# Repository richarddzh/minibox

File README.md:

# Minibox

| 目录 | 内容 |
|---|---|
| [`models`](models/module-dimensions.md) | 载板两件式外壳、错位连通键盘开孔、打印文件、尺寸与避让说明 |
| [`model-v2`](model-v2/README.md) | 低矮改版外壳：左侧喇叭、后壁偏左三角布局（开关＋双Type-C）；[截面与视角数据报告](model-v2/fit-review.html) |
| [`assets`](assets) | 开发板[尺寸与天线图](assets/esp32s3_devkit_01.jpg)、[5.08 mm 接线端子](assets/crimp_terminal.jpg)、麦克风、功放、RTC、[TFT SPI](assets/tft_spi.jpg)、[摇杆](assets/joystick.jpg)与[三键键盘](assets/keypad.jpg)参考图片（TFT 型号与当前固件配置未核对） |
| [`docs`](docs/hardware-connections.md) | 主控、屏幕和摇杆的模块参数、GPIO 接线及供电注意事项 |
| [`kicad`](kicad/README.md) | KiCad 10 双层模块载板：[正面图例](kicad/renders/minibox-carrier-front-legend.png)、[背面图例](kicad/renders/minibox-carrier-back-legend.png)、GPIO 丝印与 Gerber；实物核对后方可制板 |
| [`esp32_idf_s3n16r8`](esp32_idf_s3n16r8/README.md) | ESP32-S3 N16R8 的 LVGL 闲聊闹钟、电台、设置、游戏和可选硬件自检固件 |

固件项目参考 `C:\gitroot\talking-alarm` 的 ESP-IDF 结构，独立构建，
不依赖该目录；默认启动 LVGL 应用，保留 GPIO4/5/6/7 四键及 GPIO1/2 摇杆。
GPIO4 确认，闲聊中长按录音；GPIO5 在闲聊中按住录音、松开发送，
GPIO6 返回，GPIO7 辅助确认。原录放音自检通过菜单切换。
新增 [NES 模拟器](esp32_idf_s3n16r8/README.md#nes-游戏)，从本地 SPIFFS
加载用户自备的 `.nes` 游戏；游戏内 A/B 为动作键、X/Y 为 Select/Start，
同时长按 X+Y 退出，复用当前摇杆、ST7796 屏幕与 MAX98357 音频。
NES 画面为 **256×240 原生像素居中显示，不缩放**；目标 60 次/秒模拟、
最高 30 fps 显示，实际流畅度仍需实板确认。
支持 mapper 0、1、2、3、4、7、66、112、178、245；游戏文件用英文名称，
已配置的标题在设备上中英文双行显示。按用户要求，当前 10 个指定 ROM
随仓库提供以便异地复现；私密配置、存档和分区镜像仍不纳入 Git。
菜单四方向、NES 八方向；NES 直向容错更宽，斜向要求两轴各至少 40%、
副轴/主轴至少 85%，边界隔离区不动作。
[摇杆规则与前后区域图](esp32_idf_s3n16r8/README.md#nes-摇杆活跃区域旧版与新版)
及 [ROM 列表](esp32_idf_s3n16r8/README.md#rom-来源记录) 见固件说明。
实现取舍与验收边界见 [NES 详细计划](docs/nes-implementation-plan.md)。
当前接线为 RTC SDA=GPIO15、SCL=GPIO16，INMP441 SD=GPIO21，
MAX98357 GAIN=GPIO42、SD/MODE=GPIO47；GPIO17 悬空 NC，
摇杆按压焊脚保持 NC，GPIO42 不用于摇杆按压。

16 MiB Flash 已分配：启动/系统区域 64 KiB、应用 2 MiB、
字体文件系统 10 MiB、游戏与配置文件系统 3.9375 MiB。
分区内空闲空间不会自动借给其他分区；8 MiB PSRAM 是易失运行内存。
完整布局与更新注意事项见 [显示与存储说明](docs/display-fonts.md#文件系统分区)。
仅更新固件使用 `idf.py -p COM8 app-flash`；完整 `flash` 或 `storage-flash`
会覆盖设备 storage 中的配置和存档，须先备份。

模型文档中的导出和检查命令均在 `models` 目录执行：

```powershell
Set-Location C:\gitroot\minibox\models
python -m unittest discover -s .\tests -p test_mesh_checks.py
```

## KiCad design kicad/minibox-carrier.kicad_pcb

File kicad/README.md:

# Minibox carrier v1.2 — 2026-10-10

This is the user's actual `kicad` carrier, not the separate integrated design.
Open `minibox-carrier.kicad_pro` in KiCad 10. There is **no schematic**:
PCB DRC/net checks do not constitute ERC or schematic-parity verification.
The direct-solder revision is implemented; final review is documented in
[the Chinese HTML guide](carrier-revision.html) and [revision checklist](layout-revision-plan.md).
**Engineering-review files are not permission to manufacture or order.**

## Layout and parts

The board is **94.5 × 117 mm, R5**, four copper layers, nominal 1.6 mm.
Four Ø3.0 mm NPTH holes have **84.5 × 107 mm** center spacing;
KiCad centers are (10,8), (94.5,8), (10,115), (94.5,115) mm.
Each hole has a 3.5 mm-radius/square conservative all-layer copper keepout.
Ø3.0 mm is a tight M3 fit: check screw size/tolerance and the new enclosure.
Bounding-rectangle area is only 1.28% smaller than the old 100 × 112 mm board.

| Placement | Required reservation |
|---|---|
| ESP32 | USB left, antenna right; estimated body stays inside PCB |
| RTC | Upright, battery included in 27.5 × 12 mm reservation; 3.03 mm to ESP32 estimate |
| MAX98357 | Flat 27 × 24 mm reservation; bottom Y=72, above keycap top Y=80.5 |
| Red boundary | Y=76; upper bodies ≤74, lower operation envelopes ≥78 |
| Joystick JS1 | Vertical, center (16.8,95.5); **30 mm diameter** motion may overhang 3.20 mm; body/pad copper retain ≥1 mm to the left copper boundary |
| Microphone | Center (44.455,90.25), Ø19.5 mm envelope; top Y80.5; horizontal maximin clearance to all keycaps and joystick motion is approximately 3.40 mm |
| Four keys | Standard 19.05 mm pitch both ways; lower row moves right 1.425 mm, retaining 8.10 mm left stagger and 0.20 mm to the screw square |
| Keycaps | Maximum accepted envelope 18 × 18 mm; neighboring gap 1.05 mm |
| Wire entries | J8/J9 left, J7 right; external wire/tool clearance still requires a fit check |

SW1–SW4 use **HanElectricity CPG151101D13 / C49234235**; JS1 uses
**YTL YV13S-L7.85-B10Ka(60)-0-DL01 / C37323747**.
Their local footprints are traced to the exact linked drawings, not generic
MX/joystick substitutes. The joystick has a press mechanism but **it is intentionally
unused**; switch and mounting leads have no net; **GPIO42 now controls amplifier GAIN**.
Reference PDFs and layout images are in [`hardware_references`](../hardware_references/carrier-revision-references.md).
The exact parts lack precise supplied 3D models; renders must not be mistaken
for complete assembled-product models. Module envelopes and keycap size are
acceptance reservations, not measured/verified models.

J11/J12 cable sockets are removed. Remaining female strips: 1×22 two,
1×14 one, 1×7 one, 1×6 one, **1×3 two**, totaling seven strips/77 contacts.
J3 is two separate 1×3 sockets, row spacing 7.62 mm, **not** a normal 2×3 socket.
Three 5.08 mm screw terminals, four direct-solder switches, one direct-solder
joystick, and two 0402 resistors complete the assembly. All components install
from the front; THT leads solder from the back.
J7 is **KANGNEX WJ500V-5.08-03P-14-00A / C72334**; J8/J9 are
**WJ500V-5.08-2P / C8465**. Exact local footprints include the 0.60 mm joining
lug, 10 mm body depth, 14.07 mm height, and a tolerance-aware courtyard.
J8/J9 move left2.5/up3.94 mm from the prior version, with anchors
(11.5,48.56)/(11.5,61.06). J8's actual body top aligns with the estimated
ESP32 body bottom at Y45.97; their wire entries and electrical order are unchanged.
The selected terminal holes are **Ø1.50 mm**, with unchanged Ø2.60 mm pads
and 0.55 mm radial annular rings. No original Phoenix 3D model is reused
to impersonate the selected WJ500V; current renders show its holes/outline,
not an exact terminal body.

## GPIO and Type-C

Keys → GPIO4/5/6/7 (active-low, internal pulls); RTC SDA/SCL →15/16;
MIC_SD →21; amplifier GAIN/SD_MODE →42/47; GPIO17 is NC. I2S WS/BCLK/DIN →39/40/41;
joystick VR1/VR2 wipers →1/2; LCD remains GPIO9–14.
Actual front silkscreen identifies each module/terminal signal and its GPIO
using digits only, for example `SDA15`, `BCLK40`, `DIN41`, and `KEY1 4`.
Power pins retain `3V3`/`5V`/`GND`; disconnected pins retain `NC`.
Labels are on `F.SilkS`, not just the non-printing fabrication layer.
See [the authoritative wiring table](../docs/hardware-connections.md).
RTC front-view order is CLK/INT/SCL/SDA/3V3/GND; only functional net names
and labels changed, retaining both original copper paths. INMP441 front-view
left top-to-bottom is L/R(GND), WS39, SCK40; right is GND, 3V3, SD21.
The lower-row centre reaches approximately58% of the upper-left key width:
the requested approximate2/3 position would overlap the lower-right screw square
with18 mm keycaps. The screw exclusion takes priority without moving the hole.
The joystick's leftmost pad copper is X7.22 mm:1.22 mm from the X6 mm
copper-pour boundary and2.22 mm from the board edge. The body gap is1.05 mm.
Octal-memory GPIO35/36/37 are unused, as are USB19/20 and UART43/44.
GPIO39–42 cannot simultaneously be used for external four-wire JTAG.
Actual clone RGB firmware remains GPIO48; official v1.1 uses38, requiring
physical board identification, not an automatic firmware change.
The requested independent GPIO audit checked all44 J1/J2 pads against the
[official v1.1 J1/J3 table](https://docs.espressif.com/projects/esp-dev-kits/zh_CN/latest/esp32s3/esp32-s3-devkitc-1/user_guide_v1.1.html#j3):
no mapping errors or peripheral conflicts were found. Verify the clone's
actual pinout/RGB before production. The user has tested the actual INMP441
module and confirmed no additional SD pull-down is needed; keep the carrier,
firmware and BOM unchanged. This does not establish the module's internal
resistor arrangement or apply to other module variants.

External Type-C VBUS/GND →J8; independent CC1/CC2 →J9 pads1/2.
R1/R2 each pull their own CC to GND through **5.1 kΩ, 0402, 1%**.
Do not short CC1/CC2 or parallel Rd already present on a Type-C breakout.
This identifies a ordinary **5 V sink**, not USB-PD or a 3 A guarantee.
No USB data traces are routed. Check regulator current and USB/external-5V
backfeeding before connecting two sources.

## Routing and manufacturing review

F.Cu signals/GND; In1 continuous GND; In2 separated power corridors/GND;
B.Cu signals/GND. I2S prefers F.Cu/In1, with limited B.Cu/In2-ground-reference
branches. The router checks actual filled reference copper every ≤0.1 mm
outside necessary same-net antipads and requires one connected In1 region.
Signal vias receive nearby GND stitching. This is not a signal-integrity test.
Ground stitching was pruned from41 to23 vias after rerouting;18 redundant
vias were removed, with candidate-by-candidate connectivity/refill checks.
The current manifest records the final counts: retain return paths within
3 mm of every signal/power via and connections to separate ground-copper regions.
Do not add periodic stitching along same-layer I2S traces merely for their length;
the continuous reference plane carries their return current.

Signals/clearance **0.20/0.20 mm**, 3V3 feeders0.65 mm, 5V feeders0.80 mm;
ordinary vias **0.60/0.30 mm**. Copper-edge0.50 mm; PTH hole spacing0.45 mm;
Track-to-other-net pad clearance is **0.30 mm**, or **0.50 mm** at 5V pads.
The upper keys retain their previous positions; rightmost keycap-to-edge gap0.60 mm.
These tighter mechanical edge margins require an enclosure/cap tolerance check.
silk ≥1.0 mm with0.15 mm strokes. Header holes1.0/pads1.7 mm;
terminal holes1.5/pads2.6 mm; switch holes1.5/pads2.1 mm.
Do not treat signal width or these power feeders as a 3 A qualification.
Actual factory stackup/copper thickness, temperature rise and power bottlenecks
remain review items. [Domestic JLC capability rules](../docs/jlc-pcb-design-spec.md)
distinguish limits from recommendations.

Actual latest DRC/mechanical metrics and hashes belong in
`assembly\manifest.json` and `drc.json`;
an absent report or failed gate means export is incomplete.
Only a clean saved board may pass `export_revision.py`.
The exporter checks all plated-pad/via centers on all four copper CAM layers
against the saved PCB, and checks PTH/NPTH drill coordinates and diameters using
the same lower-left origin. This is digital alignment, not factory registration certification.
R1/R2 use verified UNI-ROYAL 0402WGF5101TCE/C25905, 5.1 kΩ ±1%;
domestic catalog stock is not reserved. Full-assembly BOM now identifies all
17 physical pieces with C numbers, including the five LAIL female-strip sizes.
Factory insertion/soldering approval, actual fit and final supply leave the BOM
**review-only**, even if DRC is clean.

### JLC placement-library mapping

Use `assembly\positions-jlc-review.csv` for the selected
domestic JLC library, together with the full BOM and the unchanged Gerber ZIP.
`positions-all-review.csv` records KiCad pad centres/footprint angles; it is
**not directly interchangeable** with the JLC file. In the factory library,
the seven female strips have a different zero angle and JS1 has a different
head datum. The exporter fits numbered library pads to actual saved PCB pads,
including the two separate J3 strips, and rejects mismatched parts or geometry.
`jlc-placement-review.json` records each angle, origin and pad-fit residual.
It also records the KiCad centre/angle and the factory origin/angle corrections.
`jlc-saved-placement.json` preserves the actual factory-saved, refreshed readback
for this board hash. Generated placements are checked against that snapshot at
the website's coordinate precision. After changing the layout, regenerate from
the new PCB: reuse library datum definitions, never copy old absolute positions.
The old snapshot is then historical evidence, not approval of the new layout.

This corrects assembly instructions, not copper or holes. Gerber has no
component-library rotation/model mapping; do not rotate PCB footprints or
change Gerber geometry to repair a factory preview. Missing J4/J6 3D models
are not missing parts. Verify the website's rotation convention and saved
positions against the actual Gerber pads before approving factory DFM.
The files remain engineering review inputs, not production approval.

Regenerate only these placement files without rerouting or re-exporting CAM:

```powershell
& 'C:\Program Files\KiCad\10.0\bin\python.exe' .\kicad\export_jlc_positions.py
```

## Current outputs and Git history

| Current revision | Purpose |
|---|---|
| `renders\assembly-layout.svg` | Reservation layout, not exact assembled geometry |
| `renders\minibox-carrier-front.png` / `back.png` | Genuine saved-board renders |
| `renders\minibox-carrier-isometric.png` | Genuine saved-board perspective |
| `renders\minibox-carrier-front-legend.png` / `back-legend.png` | Current Chinese material legends and board/hole dimensions |
| `assembly` | DRC, manifest, SMT BOM/CPL, separate THT positions, pin map |
| `fabrication` | Four-copper-layer Gerbers and separate PTH/NPTH drills |
| `fabrication\minibox-gerber-review.zip` | PCB CAM review archive |

Only fixed current paths are retained. Previous quote CSVs, dated revision
directories and older archives are recoverable from Git history, not alternate
submission inputs. The manifest records PCB/artifact hashes rather than a date
as a version identifier. Do not embed the current commit SHA in generated files:
it would describe the pre-export commit and change again when those files commit.
No order, upload, purchase or payment is authorized by these files.

## Reproducible commands

From `C:\gitroot\minibox`, after explicitly backing up the routed board:

```powershell
& 'C:\Program Files\KiCad\10.0\bin\python.exe' .\kicad\generate_board.py --replace-routed
& 'C:\Program Files\KiCad\10.0\bin\python.exe' .\kicad\route_board.py
& 'C:\Program Files\KiCad\10.0\bin\python.exe' .\kicad\prune_ground_vias.py
& 'C:\Program Files\KiCad\10.0\bin\python.exe' .\kicad\export_revision.py
```

Generation replaces routing, so its default guard refuses to overwrite tracks.
Inspect every command's result; do not continue after a failure.
For PNGs, use KiCad `pcb render --side top|bottom --quality basic` (high is optional).
Then run `python .\kicad\add_render_legends.py`; its dimensions are read
from the saved PCB, and the legends now correctly identify four copper layers.
After updating renders or documentation, run `python .\kicad\package_review.py`
to refresh `assembly\minibox-assembly-review.zip` and all artifact hashes.
Every PCB/part change requires the full export, not only the coordinate command.
The full exporter now also renders the saved board's front/back/isometric PNGs
and regenerates both Chinese dimension/legend images before packaging.
`render_source_board_sha256` binds that render batch to the exported PCB.
After partial rerouting, the pruning command removes only redundant GND vias,
refilling and checking each candidate's connectivity and actual I2S reference
copper. It preserves a GND return via within3 mm of every signal/power via.
Its reduction report is in `assembly\ground-stitching-review.json`; run the
full export afterwards to renew DRC, renders, CAM, placements and hashes.

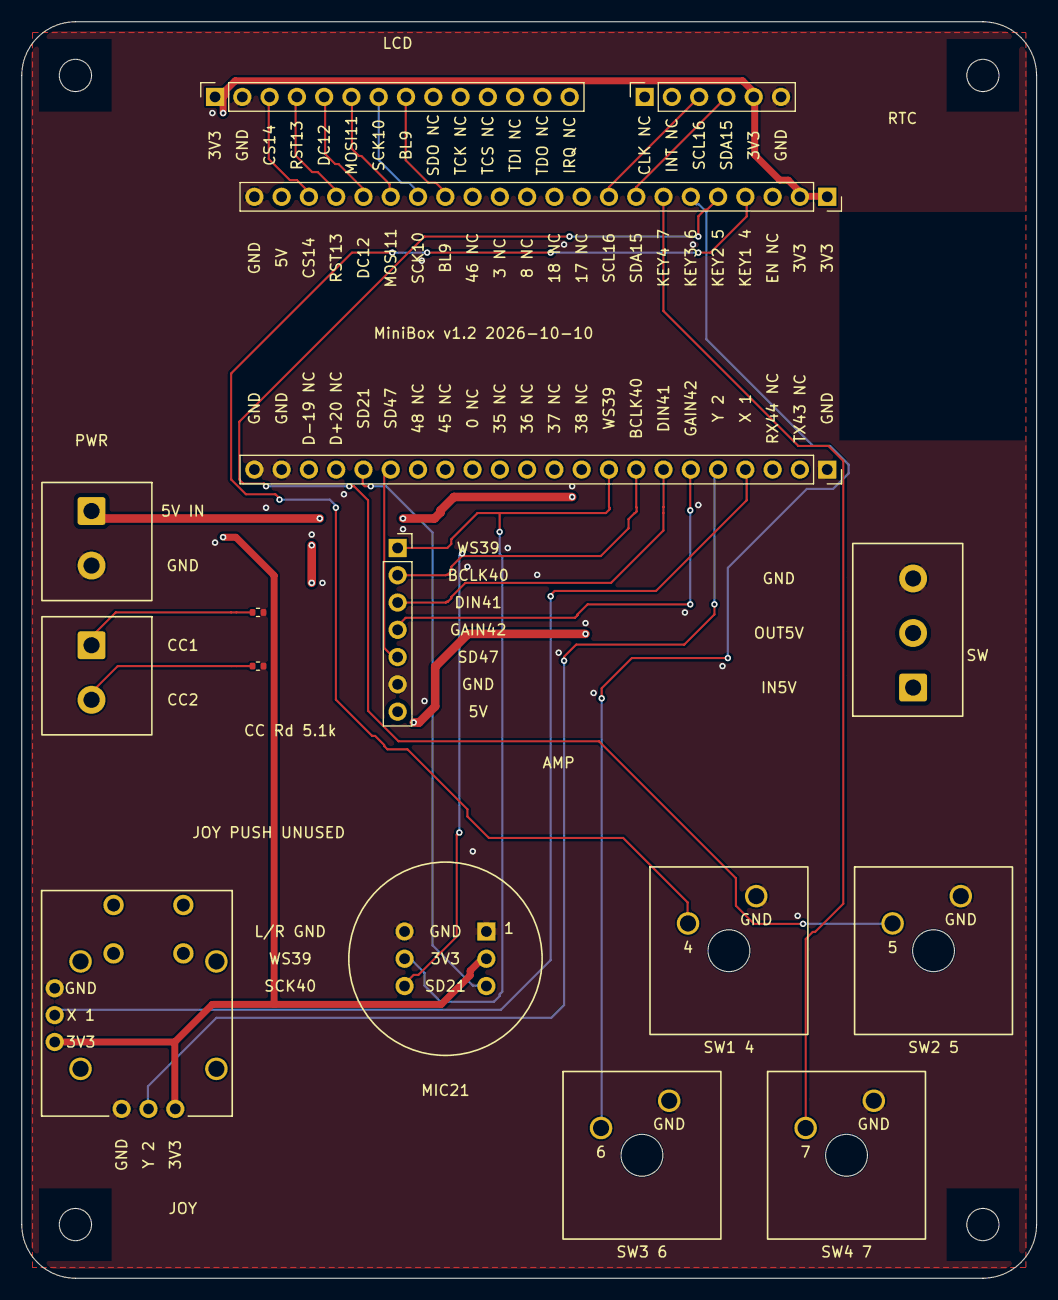
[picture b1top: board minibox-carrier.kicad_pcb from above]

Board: 4 copper layers, 94.5 x 117.0 mm, 20 parts (0 on the bottom side), 26 nets.

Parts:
H1, H2, H3, H4: M3 NPTH; MountingHole_3mm
J1: ESP32-S3 J1 - USB LEFT; PinSocket_1x22_P2.54mm_Vertical
J2: ESP32-S3 J3 - USB LEFT; PinSocket_1x22_P2.54mm_Vertical
J3: INMP441 two 1x3 sockets; INMP441_2x03_Row7.62mm
J4: MAX98357A module socket; PinSocket_1x07_P2.54mm_Vertical
J5: PCF8563T upright module; PinSocket_1x06_P2.54mm_Vertical
J6: ST7796 14-pin display; PinSocket_1x14_P2.54mm_Vertical
J7: WJ500V-5.08-03P-14-00A; WJ500V_5.08_3P
J8, J9: WJ500V-5.08-2P; WJ500V_5.08_2P
JS1: YV13S-L7.85-B10Ka(60)-0-DL01; YV13S_L7.85_B10Ka_60_0_DL01
R1, R2: 5.1k 1%; R_0402_1005Metric
SW1, SW2, SW3, SW4: CPG151101D13

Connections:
3V3: J1.1, J1.2, J3.3, J5.5, J6.1, JS1.X3, JS1.Y3
5V_IN: J7.1, J8.1
5V_SW: J1.21, J4.7, J7.2
AMP_GAIN: J2.6, J4.4
AMP_SD: J2.17, J4.5
AUDIO_DIN: J2.7, J4.3
BUTTON1: J1.4, SW1.1
BUTTON3: J1.6, SW3.1
BUTTON4: J1.7, SW4.1
GND: J1.22, J2.1, J2.21, J2.22, J3.1, J3.2, J4.6, J5.6, J6.2, J7.3, J8.2, JS1.X1, JS1.Y1, R1.2, R2.2, SW1.2, SW2.2, SW3.2, SW4.2
GPIO1: J2.4, JS1.X2
GPIO2: J2.5, JS1.Y2
I2S_BCLK: J2.8, J3.6, J4.2
I2S_WS: J2.9, J3.4, J4.1
LCD_BL: J1.15, J6.8
LCD_CS: J1.20, J6.3
LCD_DC: J1.18, J6.5
LCD_MOSI: J1.17, J6.6
LCD_RST: J1.19, J6.4
LCD_SCK: J1.16, J6.7
MIC_SD: J2.18, J3.5
RECORD: J1.5, SW2.1
RTC_SCL: J1.9, J5.3
RTC_SDA: J1.8, J5.4
USB_CC1: J9.1, R1.1
USB_CC2: J9.2, R2.1

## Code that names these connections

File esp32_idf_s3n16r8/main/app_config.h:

#pragma once

#include "sdkconfig.h"
#include <stdint.h>

#define LCD_WIDTH 480
#define LCD_HEIGHT 320
#define LCD_LED_PIN 9
#define LCD_SCK_PIN 10
#define LCD_SDI_PIN 11
#define LCD_DC_PIN 12
#define LCD_RESET_PIN 13
#define LCD_CS_PIN 14
#define LCD_SPI_HZ (CONFIG_MINIBOX_LCD_SPI_MHZ * 1000000)
#define ONBOARD_LED_PIN 48
#define AUDIO_BCLK_PIN 40
#define AUDIO_WS_PIN 39
#define MIC_SD_PIN 21
#define SPEAKER_DIN_PIN 41
#define SPEAKER_SD_MODE_PIN 47
#define SPEAKER_GAIN_PIN 42
#define AUDIO_SAMPLE_RATE 16000
#define AUDIO_MAX_SECONDS 3
#define BUTTON_1_PIN 4
#define RECORD_BUTTON_PIN 5
#define BUTTON_3_PIN 6
#define BUTTON_4_PIN 7
#define BUTTON_COUNT 4
#define RTC_SDA_PIN 15
#define RTC_SCL_PIN 16

#define MINIBOX_STRINGIFY_INNER(value) #value
#define MINIBOX_STRINGIFY(value) MINIBOX_STRINGIFY_INNER(value)
#define BUTTON_GPIO_LABELS "GPIO" MINIBOX_STRINGIFY(BUTTON_1_PIN) "/" \
                          MINIBOX_STRINGIFY(RECORD_BUTTON_PIN) "/" \
                          MINIBOX_STRINGIFY(BUTTON_3_PIN) "/" \
                          MINIBOX_STRINGIFY(BUTTON_4_PIN)
#define RECORD_GPIO_LABEL "GPIO" MINIBOX_STRINGIFY(RECORD_BUTTON_PIN)

#define JOYSTICK_X_PIN CONFIG_MINIBOX_JOYSTICK_X_PIN
#define JOYSTICK_Y_PIN CONFIG_MINIBOX_JOYSTICK_Y_PIN
#define JOYSTICK_K_PIN (-1)
#ifdef CONFIG_MINIBOX_JOYSTICK_K_ACTIVE_LOW
#define JOYSTICK_K_ACTIVE_LEVEL 0
#else
#define JOYSTICK_K_ACTIVE_LEVEL 1
#endif

_Static_assert(JOYSTICK_X_PIN != JOYSTICK_Y_PIN &&
               JOYSTICK_X_PIN != JOYSTICK_K_PIN &&
               JOYSTICK_Y_PIN != JOYSTICK_K_PIN,
               "Joystick pins must be distinct");
_Static_assert(JOYSTICK_X_PIN >= 1 && JOYSTICK_X_PIN <= 10 &&
               JOYSTICK_Y_PIN >= 1 && JOYSTICK_Y_PIN <= 10,
               "ESP32-S3 joystick axes require ADC1 GPIO1-10, not GPIO40/41");
_Static_assert(JOYSTICK_X_PIN != BUTTON_1_PIN &&
               JOYSTICK_X_PIN != RECORD_BUTTON_PIN &&
               JOYSTICK_X_PIN != BUTTON_3_PIN &&
               JOYSTICK_X_PIN != BUTTON_4_PIN &&
               JOYSTICK_Y_PIN != BUTTON_1_PIN &&
               JOYSTICK_Y_PIN != RECORD_BUTTON_PIN &&
               JOYSTICK_Y_PIN != BUTTON_3_PIN &&
               JOYSTICK_Y_PIN != BUTTON_4_PIN &&
               JOYSTICK_K_PIN != BUTTON_1_PIN &&
               JOYSTICK_K_PIN != RECORD_BUTTON_PIN &&
               JOYSTICK_K_PIN != BUTTON_3_PIN &&
               JOYSTICK_K_PIN != BUTTON_4_PIN,
               "Joystick pins must not conflict with keypad pins");
_Static_assert(MIC_SD_PIN != RTC_SDA_PIN && MIC_SD_PIN != RTC_SCL_PIN &&
               SPEAKER_SD_MODE_PIN != BUTTON_4_PIN &&
               SPEAKER_GAIN_PIN != RTC_SDA_PIN && SPEAKER_GAIN_PIN != RTC_SCL_PIN &&
               SPEAKER_SD_MODE_PIN != RTC_SDA_PIN && SPEAKER_SD_MODE_PIN != RTC_SCL_PIN,
               "Revised carrier GPIOs must not share peripheral functions");
_Static_assert(JOYSTICK_X_PIN != SPEAKER_SD_MODE_PIN &&
               JOYSTICK_Y_PIN != SPEAKER_SD_MODE_PIN &&
               JOYSTICK_K_PIN != SPEAKER_SD_MODE_PIN &&
               JOYSTICK_X_PIN != SPEAKER_GAIN_PIN &&
               JOYSTICK_Y_PIN != SPEAKER_GAIN_PIN &&
               JOYSTICK_K_PIN != SPEAKER_GAIN_PIN,
               "Joystick pins must not conflict with amplifier control pins");
_Static_assert(JOYSTICK_K_PIN != AUDIO_BCLK_PIN &&
               JOYSTICK_K_PIN != AUDIO_WS_PIN &&
               JOYSTICK_K_PIN != MIC_SD_PIN &&
               JOYSTICK_K_PIN != SPEAKER_DIN_PIN &&
               JOYSTICK_K_PIN != RTC_SDA_PIN &&
               JOYSTICK_K_PIN != RTC_SCL_PIN,
               "Joystick button must not share I2S or RTC pins");

/* Business logic uses the same physical peripherals as hardware diagnostics. */
#define APP_UI_W 320
#define APP_UI_H 240
#define APP_ONBOARD_RGB_PIN ONBOARD_LED_PIN
#define APP_BUTTON_DEBOUNCE_MS 30
#define APP_BUTTON_LONG_PRESS_MS 800
#define APP_MIC_BCLK_PIN AUDIO_BCLK_PIN
#define APP_MIC_LRCK_PIN AUDIO_WS_PIN
#define APP_MIC_DATA_PIN MIC_SD_PIN
#define APP_SPK_BCLK_PIN AUDIO_BCLK_PIN
#define APP_SPK_LRCK_PIN AUDIO_WS_PIN
#define APP_SPK_DATA_PIN SPEAKER_DIN_PIN
#define APP_VOICE_SAMPLE_RATE 16000U
#define APP_MIC_CAPTURE_RATE 16000U
#define APP_MIC_DIGITAL_GAIN 1
#define APP_VOICE_MAX_RECORD_MS 10000U
#define APP_AUDIO_ARENA_BYTES (64 * 1024)
#define APP_WIFI_CONNECT_TIMEOUT_MS 20000U
#define APP_WIFI_RETRY_MS 5000U
#define APP_TIME_REFRESH_MS 86400000U

#define APP_DOUBAO_ASR_URL \
    "wss://openspeech.bytedance.com/api/v3/sauc/bigmodel_nostream"
#define APP_DOUBAO_ASR_RESOURCE_ID "volc.seedasr.sauc.duration"
#define APP_DOUBAO_AGENT_URL \
    "https://open.feedcoopapi.com/agent_api/agent/chat/completion"
#define APP_DOUBAO_AGENT_BOT_ID "7647087216547694086"
#define APP_DOUBAO_TTS_URL \
    "https://openspeech.bytedance.com/api/v3/tts/unidirectional"
#define APP_DOUBAO_TTS_RESOURCE_ID "seed-icl-2.0"
#define APP_DOUBAO_TTS_SPEAKER "S_yOMisdm22"
#define APP_DOUBAO_TTS_SAMPLE_RATE APP_VOICE_SAMPLE_RATE

#define APP_SPIFFS_BASE_PATH "/spiffs"
#define APP_WIFI_CONFIG_PATH "/spiffs/wifi_config.txt"
#define APP_WIFI_PROFILES_PATH "/spiffs/wifi_profiles.bin"
#define APP_SECRETS_CONFIG_PATH "/spiffs/app_secrets.txt"
#define APP_PROVISION_AP_SSID "Minibox-Setup"
#define APP_PROVISION_AP_PASSWORD "minibox-setup"
#define APP_PROVISION_AP_CHANNEL 1
#define APP_PROVISION_AP_MAX_CONN 4

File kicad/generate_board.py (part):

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    "45 NC", "48 NC", "SD47", "SD21", "D+20 NC", "D-19 NC", "GND", "GND",
]
J2_NETS = [
    "GND", None, None, "GPIO1", "GPIO2", "AMP_GAIN", "AUDIO_DIN", "I2S_BCLK", "I2S_WS",
    None, None, None, None, None, None, None, "AMP_SD", "MIC_SD", None, None, "GND", "GND",
]

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power = terminal("J8", 2, 11.5, 48.56, ["5V_IN", "GND"], 270)
cc = terminal("J9", 2, 11.5, 61.06, ["USB_CC1", "USB_CC2"], 270)
joy = load("JS1", "Minibox", "YV13S_L7.85_B10Ka_60_0_DL01", 16.8, 95.5,
           {"X1": "GND", "X2": "GPIO1", "X3": "3V3",
            "Y1": "GND", "Y2": "GPIO2", "Y3": "3V3"},
           "YV13S-L7.85-B10Ka(60)-0-DL01", 270)
for i, (x, y) in enumerate(KEY_CENTERS, 1):
    load(f"SW{i}", "Minibox", "CPG151101D13", x, y,
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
